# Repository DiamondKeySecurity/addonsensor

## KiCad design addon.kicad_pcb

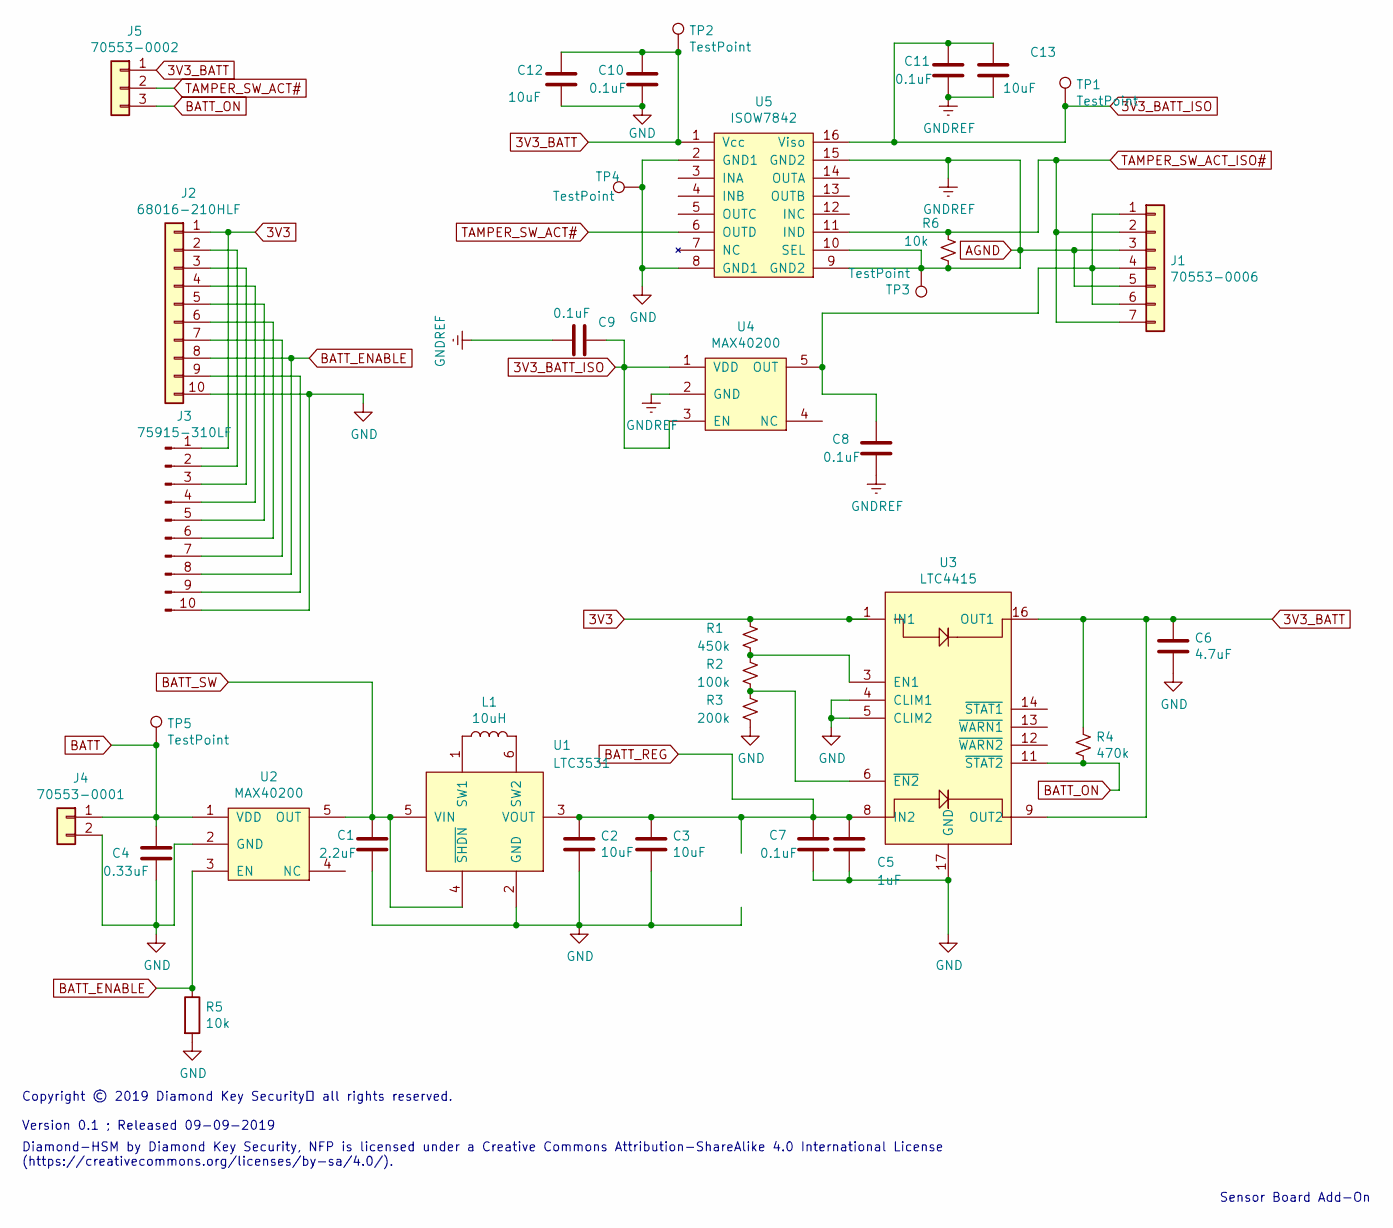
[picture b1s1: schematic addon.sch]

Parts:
C1: 2.2uF; C_0805
C2, C3, C12, C13: 10uF; C_0805
C4: 0.33uF; C_0402
C5: 1uF; C_0603
C6: 4.7uF; C_0805
C7, C8, C9, C10, C11: 0.1uF; C_0402
J1: 70553-0006; SL 70553-07
J2: 68016-210HLF; 75915
J3: 75915-310LF; 75915
J4: 70553-0001; Molex_KK-6410-02_02x2.54mm_Straight
J5: 70553-0002; Molex_KK-6410-03_03x2.54mm_Straight
L1: 10uH; L_1812
R1: 450k; R_0603
R2: 100k; R_0603
R3: 200k; R_0603
R4: 470k; R_0603
R5: 10k; R_0805
R6: 10k; R_0603
TP1, TP2, TP3, TP4: TestPoint; Measurement_Point_Square-SMD-Pad_Small
TP5: TestPoint; Pin_Header_Angled_1x01_Pitch2.54mm
U1: LTC3531; TSOT-23-6
U2, U4: MAX40200; SOT-23-5
U3: LTC4415; MSOP-16-1EP-VIA_3x4mm_Pitch0.5mm
U5: ISOW7842; SOIC-16W_7.5x10.3mm_Pitch1.27mm

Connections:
3V3: J2.1, J3.1, R1.1, U3.1 (IN1)
3V3_BATT: C6.1, C10.1, C12.1, J5.1, R4.1, TP2.1, U3.9 (OUT2), U3.16 (OUT1), U5.1 (Vcc); also elsewhere on the board
3V3_BATT_ISO: C9.1, C11.1, C13.1, TP1.1, U4.1 (VDD), U4.3 (EN), U5.16 (Viso); also elsewhere on the board
AGND: C8.2, C9.2, C11.2, C13.2, J1.3, J1.5, R6.2, TP3.1, U4.2 (GND), U5.9 (GND2), U5.10 (SEL), U5.15 (GND2)
BATT: C4.1, J4.1, TP5.1, U2.1 (VDD)
BATT_ENABLE: J2.8, J3.8, R5.1, U2.3 (EN)
BATT_ON: J5.3, R4.2, U3.11 (~STAT2)
BATT_REG: C2.1, C3.1, C5.1, C7.1, U1.3 (VOUT), U3.8 (IN2)
BATT_SW: C1.1, U1.4 (~SHDN), U1.5 (VIN), U2.5 (OUT)
GND: C1.2, C2.2, C3.2, C4.2, C5.2, C6.2, C7.2, C10.2, C12.2, J2.10, J3.10, J4.2, R3.2, R5.2, TP4.1, U1.2 (GND), U2.2 (GND), U3.4 (CLIM1), U3.5 (CLIM2), U3.17 (GND), U5.2 (GND1), U5.8 (GND1)
unnamed: C8.1, J1.1, J1.4, J1.6, U4.5 (OUT)
unnamed: J2.2, J3.2
unnamed: J2.3, J3.3
unnamed: J2.4, J3.4
unnamed: J2.5, J3.5
unnamed: J2.6, J3.6
unnamed: J2.7, J3.7
unnamed: J2.9, J3.9
unnamed: L1.1, U1.6 (SW2)
unnamed: L1.2, U1.1 (SW1)
unnamed: R1.2, R2.1, U3.3 (EN1)
unnamed: R2.2, R3.1, U3.6 (~EN2)
TAMPER_SW_ACT#: J5.2, U5.6 (OUTD)
TAMPER_SW_ACT_ISO#: J1.2, J1.7, R6.1, U5.11 (IND)

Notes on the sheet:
Sensor Board Add-On
Diamond-HSM by Diamond Key Security, NFP is licensed under a Creative Commons Attribution-ShareAlike 4.0 International License (https://creativecommons.org/licenses/by-sa/4.0/).
Copyright © 2019 Diamond Key Security™ all rights reserved. Version 0.1 ; Released 09-09-2019

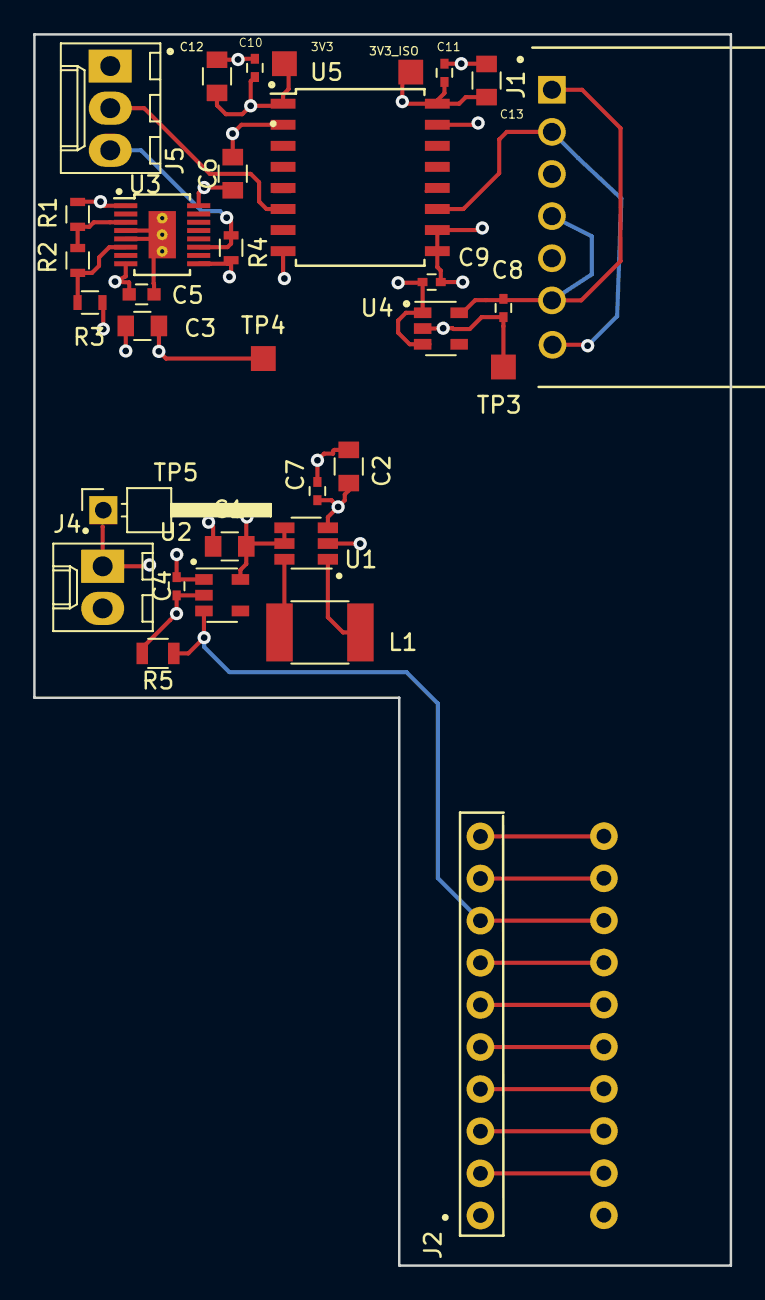
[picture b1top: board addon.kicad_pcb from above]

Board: 4 copper layers, 42.0 x 74.2 mm, 34 parts (1 on the bottom side), 24 nets.

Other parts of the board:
3V3, 3V3_ISO: TestPoint; Measurement_Point_Square-SMD-Pad_Small

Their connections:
3V3_BATT: 3V3.1; also elsewhere on the board
3V3_BATT_ISO: 3V3_ISO.1; also elsewhere on the board

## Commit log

2019-05-21 footprint update
2019-05-21 resistors
2019-05-21 3531 additions
2019-05-21 tps22969
2019-05-21 caps value
2019-05-28 alpha circuits
2019-05-28 j1 wiring
2019-05-28 ADD ISO7041
2019-05-28 add iso7041 to schematic
2019-05-28 ADDED MAX40200
2019-05-29 added 40200 as power switch
2019-05-29 adding footprints
2019-05-29 added bypass caps
2019-05-29 added flying leads header
2019-05-30 added references
2019-05-30 removed external components
2019-05-31 added Sl 7 pin footprint and removed J2
2019-05-31 30 min
2019-05-31 30 min update
2019-05-31 layout update
2019-05-31 board outline complete
2019-06-03 moved batt sw
2019-06-03 layout updates
2019-06-03 ground plane
2019-06-04 addded pns
2019-06-04 drc fixes
2019-08-01 added pull down for battery switch, reconfigured resitive totem for u3 and replaced digital isolator
2019-08-01 fixed isow7402 symbol
2019-08-06 update zones
2019-08-06 fixed test point pads
2019-08-09 added test points and 10u caps for ISoW7842
2019-09-18 last updates to addon including licensing info
2019-09-20 updated license text
